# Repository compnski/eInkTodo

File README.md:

# E-Ink Todo List

A mess of Arduino C++, a local python proxy and some google apps script.

## Google Apps Script
This is used to get the calendar events and format into a easily parsable list. Copy the code from googleAppScript.gs into a project.
Then update the calendarId with your own, deploy it as a webapp and you're in business!
https://script.google.com/

## todoProxy.py
I was having an awful lot of trouble connecting to google via SSL. In particular, the apps script webapp sends a few Location header redirects and my ESP32 would get stuck after following one or two. No idea why.

My fix was to set up a local proxy on my computer. This also removes the need for an SSL client, removing one more troublesome part from the equation.

Update the taskURL with the URL of your google app script webapp, and you're good to go.

The /done/ stuff is hardcoded and not ready yet, eventually it'll take the event Id to mark it complete.

## Arduino code
This stuff is a huge pile of spaghetti C++. It's been maybe 10 years since I last wrote anything with C++ and it shows.
I've also not done too much Arduino, so have no idea how to setup the file structure.

For this, symlink todo.cpp into your Arduino folder as anything with a .ino file extension. Then add your SSID/password + taskURL. (Or create a secrets.h and copy/symlink that over too).

Then symlink the two library folders, HttpClient and TodoList into ~/Arduino/libraries, they should be found automatically.

You'll also need the ESP32 SDK and the waveshare SDK -- I used instructions from the waveshare wiki -- https://www.waveshare.com/wiki/7.5inch_HD_e-Paper_HAT_(B).

## Troubleshooting
The wifi only seems to connect like 1 in 100 times. It worked great in the prototype step, now, not so much. Good luck!

## TODO

1. Fetch temp / weather ?
1. Look into adding lines across for style
1. Checkmark for completed tasks
1. Red color for overdue tasks
1. Read buttons for done
1. Flash LED on overdue
1. Fix spacing and all that
1. Speaker / sound
1. Neopixels on top
1. Korean word of the day?? (First todo?)

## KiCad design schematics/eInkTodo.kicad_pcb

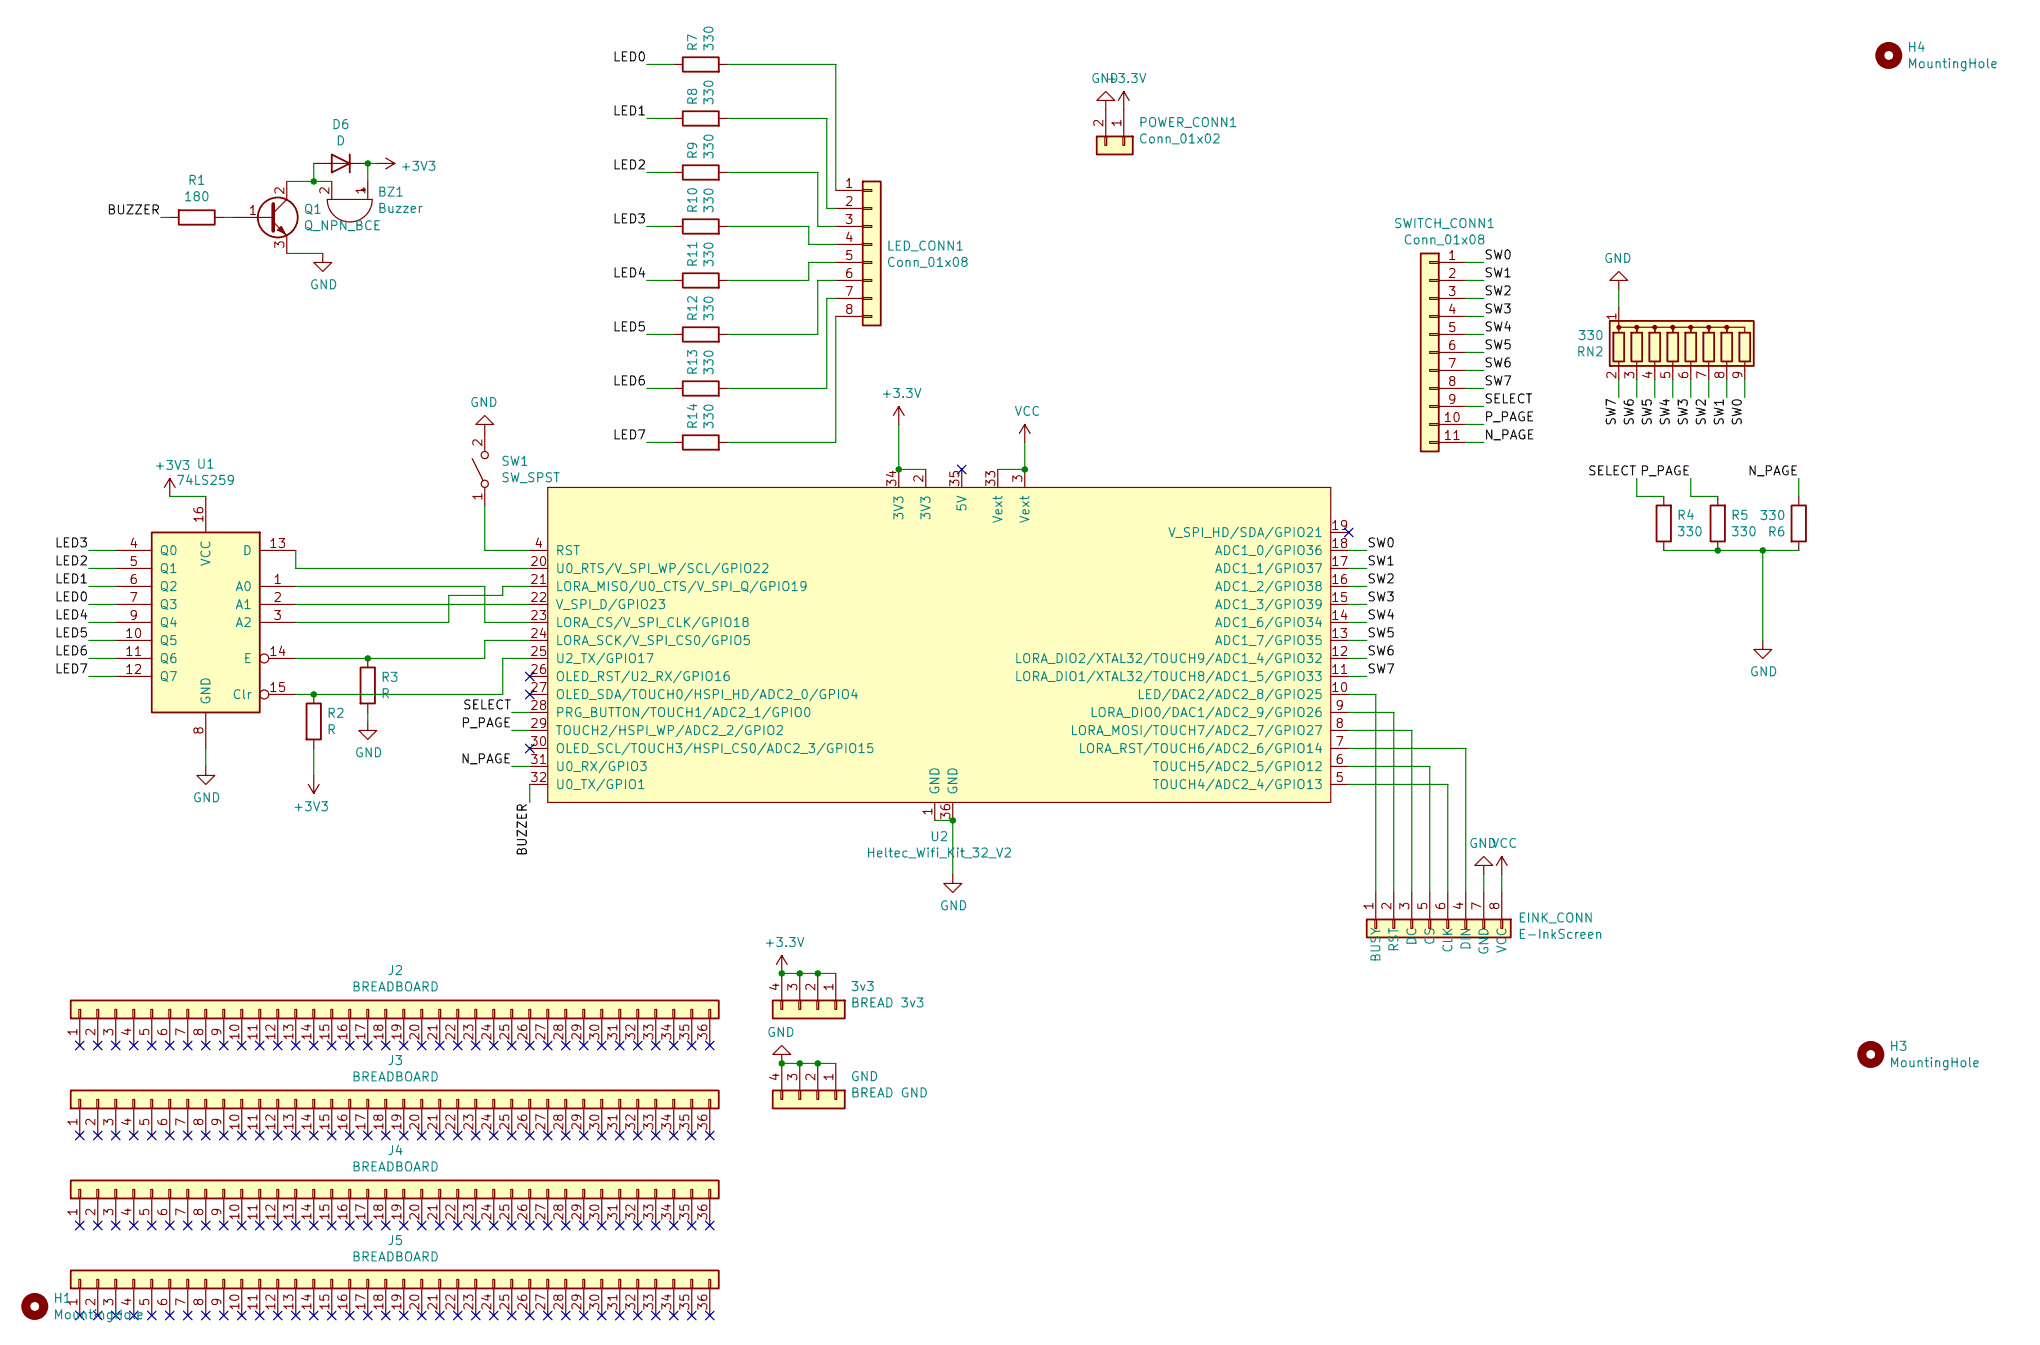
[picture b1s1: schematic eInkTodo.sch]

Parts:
3v3: BREAD 3v3; PinHeader_1x04_P2.54mm_Vertical
BZ1: Buzzer; MagneticBuzzer_CUI_CST-931RP-A
D6: D; D_DO-41_SOD81_P10.16mm_Horizontal
EINK_CONN: E-InkScreen; PinHeader_1x08_P2.54mm_Horizontal
GND: BREAD GND; PinHeader_1x04_P2.54mm_Vertical
H1, H3, H4: MountingHole; MountingHole_2.7mm_M2.5
J2, J3, J4, J5: BREADBOARD; PinHeader_1x36_P2.54mm_Vertical
LED_CONN1: Conn_01x08; PinHeader_1x08_P2.54mm_Horizontal
POWER_CONN1: Conn_01x02; PinHeader_1x02_P2.54mm_Horizontal
Q1: Q_NPN_BCE; TO-92_HandSolder
R1: 180; R_Axial_DIN0207_L6.3mm_D2.5mm_P10.16mm_Horizontal
R2, R3: R; R_Axial_DIN0207_L6.3mm_D2.5mm_P10.16mm_Horizontal
R4, R5, R6, R7, R8, R9, R10, R11, R12, R13, R14: 330; R_Axial_DIN0207_L6.3mm_D2.5mm_P10.16mm_Horizontal
RN2: 330; R_Array_SIP9
SW1: SW_SPST; PinHeader_1x02_P2.54mm_Vertical
SWITCH_CONN1: Conn_01x08; PinHeader_1x11_P2.54mm_Horizontal
U1: 74LS259; DIP-16_W7.62mm_LongPads
U2: Heltec_Wifi_Kit_32_V2; Heltec_WiFi_Kit_32

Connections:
/BUZZER: R1.2, U2.32 (U0_TX/GPIO1)
/LED0: R7.1, U1.7 (Q3)
/LED1: R8.1, U1.6 (Q2)
/LED2: R9.1, U1.5 (Q1)
/LED3: R10.1, U1.4 (Q0)
/LED4: R11.1, U1.9 (Q4)
/LED5: R12.1, U1.10 (Q5)
/LED6: R13.1, U1.11 (Q6)
/LED7: R14.1, U1.12 (Q7)
/N_PAGE: R6.1, SWITCH_CONN1.11, U2.31 (U0_RX/GPIO3)
/P_PAGE: R5.2, SWITCH_CONN1.10, U2.29 (TOUCH2/HSPI_WP/ADC2_2/GPIO2)
/SELECT: R4.2, SWITCH_CONN1.9, U2.28 (PRG_BUTTON/TOUCH1/ADC2_1/GPIO0)
/SW0: RN2.9 (R8), SWITCH_CONN1.1, U2.18 (ADC1_0/GPIO36)
/SW1: RN2.8 (R7), SWITCH_CONN1.2, U2.17 (ADC1_1/GPIO37)
/SW2: RN2.7 (R6), SWITCH_CONN1.3, U2.16 (ADC1_2/GPIO38)
/SW3: RN2.6 (R5), SWITCH_CONN1.4, U2.15 (ADC1_3/GPIO39)
/SW4: RN2.5 (R4), SWITCH_CONN1.5, U2.14 (ADC1_6/GPIO34)
/SW5: RN2.4 (R3), SWITCH_CONN1.6, U2.13 (ADC1_7/GPIO35)
/SW6: RN2.3 (R2), SWITCH_CONN1.7, U2.12 (LORA_DIO2/XTAL32/TOUCH9/ADC1_4/GPIO32)
/SW7: RN2.2 (R1), SWITCH_CONN1.8, U2.11 (LORA_DIO1/XTAL32/TOUCH8/ADC1_5/GPIO33)
GND: EINK_CONN.7 (GND), GND.1, GND.2, GND.3, GND.4, POWER_CONN1.2, Q1.3 (E), R3.2, R4.1, R5.1, R6.2, RN2.1 (common), SW1.2 (B), U1.8 (GND), U2.1 (GND), U2.36 (GND); also elsewhere on the board
unnamed: BZ1.2 (+), D6.2 (A), Q1.2 (C)
unnamed 22: EINK_CONN.1 (BUSY), U2.10 (LED/DAC2/ADC2_8/GPIO25); also elsewhere on the board
unnamed 23: EINK_CONN.2 (RST), U2.9 (LORA_DIO0/DAC1/ADC2_9/GPIO26); also elsewhere on the board
unnamed 24: EINK_CONN.3 (DC), U2.8 (LORA_MOSI/TOUCH7/ADC2_7/GPIO27); also elsewhere on the board
unnamed 25: EINK_CONN.4 (DIN), U2.7 (LORA_RST/TOUCH6/ADC2_6/GPIO14); also elsewhere on the board
unnamed 26: EINK_CONN.5 (CS), U2.6 (TOUCH5/ADC2_5/GPIO12); also elsewhere on the board
unnamed 27: EINK_CONN.6 (CLK), U2.5 (TOUCH4/ADC2_4/GPIO13); also elsewhere on the board
unnamed: LED_CONN1.1, R7.2
unnamed: LED_CONN1.2, R8.2
unnamed: LED_CONN1.3, R9.2
unnamed: LED_CONN1.4, R10.2
unnamed: LED_CONN1.5, R11.2
unnamed: LED_CONN1.6, R12.2
unnamed: LED_CONN1.7, R13.2
unnamed: LED_CONN1.8, R14.2
unnamed: Q1.1 (B), R1.1
unnamed: R2.1, U1.15 (Clr), U2.25 (U2_TX/GPIO17)
unnamed: R3.1, U1.14 (E), U2.24 (LORA_SCK/V_SPI_CS0/GPIO5)
unnamed: SW1.1 (A), U2.4 (RST)
unnamed: U1.1 (A0), U2.23 (LORA_CS/V_SPI_CLK/GPIO18)
unnamed: U1.2 (A1), U2.22 (V_SPI_D/GPIO23)
unnamed: U1.3 (A2), U2.21 (LORA_MISO/U0_CTS/V_SPI_Q/GPIO19)
unnamed: U1.13 (D), U2.20 (U0_RTS/V_SPI_WP/SCL/GPIO22)
VCC: EINK_CONN.8 (VCC), U2.3 (Vext), U2.33 (Vext); also elsewhere on the board

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
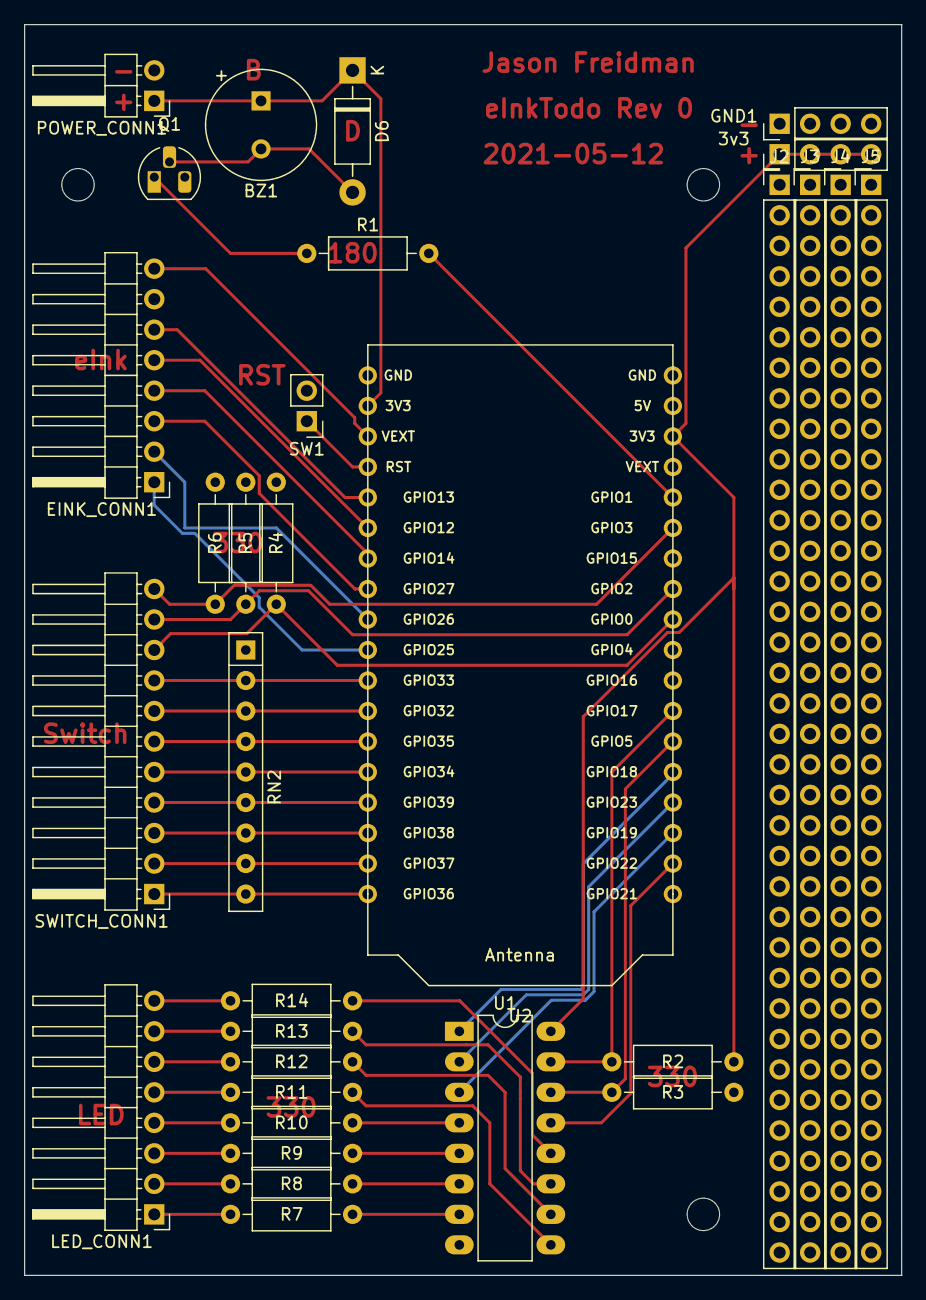
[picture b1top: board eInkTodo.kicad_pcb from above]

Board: 2 copper layers, 73.0 x 104.1 mm, 34 parts (0 on the bottom side), 46 nets.

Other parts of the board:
EINK_CONN1: E-InkScreen; PinHeader_1x08_P2.54mm_Horizontal
GND1: BREAD GND; PinHeader_1x04_P2.54mm_Vertical

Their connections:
GND: EINK_CONN1.7, GND1.1, GND1.2, GND1.3, GND1.4; also elsewhere on the board
unnamed 22: EINK_CONN1.1; also elsewhere on the board
unnamed 23: EINK_CONN1.2; also elsewhere on the board
unnamed 24: EINK_CONN1.3; also elsewhere on the board
unnamed 25: EINK_CONN1.4; also elsewhere on the board
unnamed 26: EINK_CONN1.5; also elsewhere on the board
unnamed 27: EINK_CONN1.6; also elsewhere on the board
VCC: EINK_CONN1.8; also elsewhere on the board

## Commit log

2021-05-08 Start schematic design for main board
2021-05-08 Initial CAD for case
2021-05-08 Add button rest
2021-05-08 Add missing schematic libraries. Were git-ignored.
2021-05-09 Update eink screen to match actual size
2021-05-09 Almost complete schematic. Use Net labels for clarity. Add a buzzer
2021-05-13 Cleanup + factor e-ink display into a separate class.
    Also clean up how button and LEDs work
2021-05-13 Finish board layout
2021-05-14 ignore generated gerber files
2021-05-14 Fix code to actually compile and run
2021-05-14 Adjust height to fit frame
2021-05-15 fix task parsing
2021-05-15 Mark events done by eventId
2021-05-15 Add latch for LEDs
2021-05-15 Update pin #s
